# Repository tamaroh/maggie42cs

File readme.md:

# Maggie42cs

Maggie42csは42キー分割型の自作キーボードです。
- 左右対称カラムスタッガード
- Alice配列に似た、自然にハの字に手が配置されるデザイン
- MX Cherry 互換スイッチ、Kailh Choc v1, v2スイッチの3種に対応
- Extension キーはキーキャップセットで揃いやすい1.25U, 1.5Uに対応

## 必要なもの

| 部品名称                | 数量（両手分）                 | 備考                                   | 主な購入先                                                          |
| ----------------------  | ------------------------------ | -------------------------------------- | ------------------------------------------------------------------- |
| PCB                     | 1                              | サポートを折って左右に分けます         |                                                                     |
| トッププレート          | 2                              | 猫のシルエットがあるのが左側           |                                                                     |
| ボトムプレート          | 2                              | 左右の差はありません                   |                                                                     |
| ネジ                    | 24                             | M2                                     |                                                                     |
| 丸スペーサー            | 12                             | 5mm or 7.5mm                           |                                                                     |
| ゴム足                  | 8                              |                                        |                                                                     |
| スイッチソケット        | 42                             | Cherry MX / Kailh choc 対応のもの      | [TALP KEYBOARD](https://shop.talpkeyboard.com) など                 |
| メカニカルスイッチ      | 42                             | Cherry MX / Kailh choc V1 / V2 対応*   | [遊舎工房](https://shop.yushakobo.jp/collections/all-switches) など |
| キーキャップ            | 1U x 33, 1.25U x 7, 1.5U x 2   | スイッチに対応したもの                 | [遊舎工房](https://shop.yushakobo.jp/collections/keycaps) など      |
| TRSコネクター           | 2                              | PJ-399B-6A                             | [LCSC](https://www.lcsc.com/) など                                  |
| 3.5mmオーディオケーブル | 1                              | TRRS（4極）またはTRS（3極）            | [TALP KEYBOARD](https://shop.talpkeyboard.com) など                 |
| USBケーブル             | 1                              | 機器側がTypeCのもの                    | 家電量販店など                                                      |

## 使用する工具など

- はんだ付け工具
  - こて、こて台、こて先クリーナー、はんだ線など
- 精密ドライバー

## あると便利なもの

- ピンセット
- キースイッチプラー
- キーキャッププラー
- はんだ吸い取り線または吸い取り器
- 絶縁耐熱テープ
- 
## 製作手順

1. PCBのサポート部分を折り取ります。折った部分のデコボコが気になる場合はやすりなどで削ってください。
   
1. ソケットをはんだ付けします。  
   MXスイッチ用のソケットは上側、Chocスイッチ用のソケットは下側に設置します。  
   印刷に合わせて、スイッチの穴を塞がないようにします。
   
1. TRSコネクターをはんだ付けします。  
   ずれやすいのでテープなどで固定してください。  
   
1. ファームウェアのファイル（.uf2）をダウンロードします。  
   https://github.com/tamaroh/maggie42cs/releases/tag/V2.0.2
1. （片側ずつ両方とも）USBケーブルを接続して、以下のいずれかの方法で `RPI-RP2` リムーバブルドライブをマウントさせます。
   1. BOOTSELボタンを押しながら、USBケーブルを接続します。
   1. USBケーブルを接続してから、BOOTSELボタンを押しながらRESETボタンを押します。
   1. 左側はTABキー、右側はYキーを押したままUSBケーブルを接続します（キースイッチ装着済みの場合）。
   
1. （片側ずつ両方とも）マウントされた `RPI-RP2` ドライブ内にファームウェアのファイルをコピーして保存します。
   自動的にマウントが解除され、キーボードが再起動します。
   再起動したら、一度USBケーブルを抜いてください。
1. キースイッチを数個、先にキープレートに差し込みます。キープレートの表裏は印字以外にはありません。
   
1. スイッチのピンがソケットに合うように上からまっすぐ抑え、基板と接続して位置を合わせます。

1. 残りのスイッチを差し込みます。ソケットとスイッチを指で挟み込むようにして、ソケットに確実に差し込みます。
1. 基板を裏返し、ソケットからスイッチの端子の先端が見えることを確認してください。見えない場合はスイッチのピンが曲がっているか、ソケットの不良です。
   
1. ネジとスペーサーをトッププレートにネジ止めします。(片側6箇所) 
1. ボトムプレートをネジ止めし、ゴム足を取り付けます。
1. キーキャップを取り付けます。
1. TRRSケーブルを接続して、できあがり

## キーマップを変更する

Maggie42は[Remap](https://remap-keys.app)によるキーマップ変更に対応しています。  
ハードウェア接続のあとJSONファイルを要求される場合は[ファームウェアと同じ場所](https://github.com/tamaroh/maggie42cs/releases/tag/V2.0.2)からダウンロードして使用してください。

## 注意事項

- 必要な手順や部品の種類・数はアップデートによって変更になる場合があります。
- 本ビルドガイドの写真の一部は製品と異なる場合があります。

## 実装の差異について

キーケット2026にて販売した一部のキットは、製作の時期により差異があります。
- 4極の3.5mmコネクターを使用しています（はんだ実装済みです）。TRS（3極）ケーブルではなくTRRS（4極）ケーブルが必要です。
- 左右でPCBの印字の色が異なります。
  
- 手順通りのファームウェアとは異なります。書き込み済みで販売いたしましたが、再度セットアップする場合は[V2.0.0のファームウェア](https://github.com/tamaroh/maggie42cs/releases/tag/V2.0.0)を使用してください。
- Remapにアクセスした際は「maggie42csv2」と表示されます。

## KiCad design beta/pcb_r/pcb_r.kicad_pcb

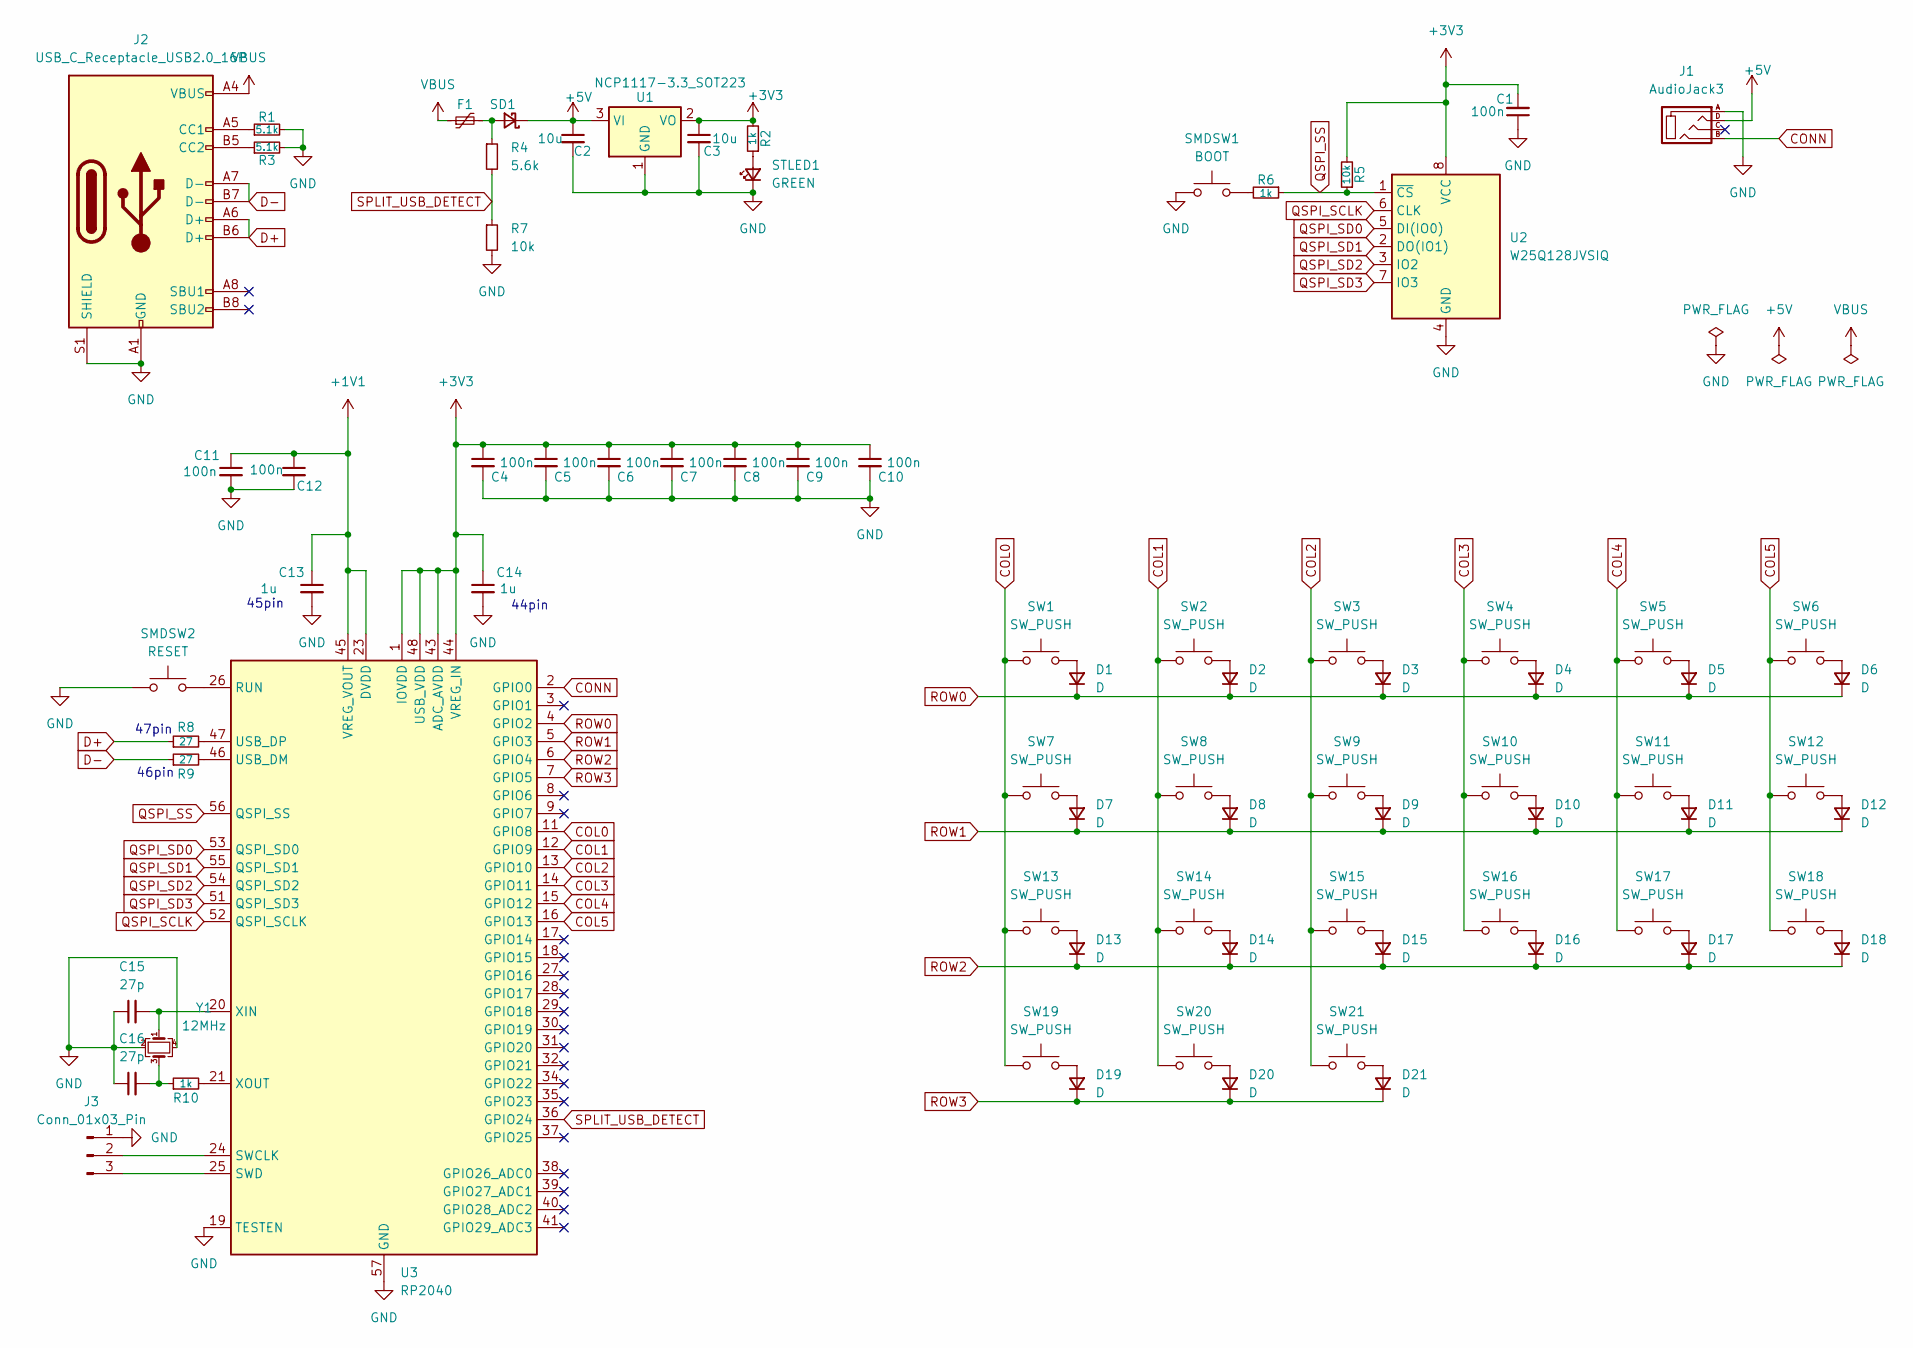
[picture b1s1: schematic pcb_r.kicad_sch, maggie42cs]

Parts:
C1, C4, C5, C6, C7, C8, C9, C10, C11, C12: 100n; C_0402_1005Metric; LCSC C1525
C2, C3: 10u; C_0402_1005Metric; LCSC C15525
C13, C14: 1u; C_0402_1005Metric; LCSC C52923
C15, C16: 27p; C_0402_1005Metric; LCSC C1557
D1, D2, D3, D4, D5, D6, D7, D8, D9, D10, D11, D12, D13, D14, D15, D16, D17, D18, D19, D20, D21: D; D_SOD-123; LCSC C81598
F1: Fuse_0603_1608Metric; LCSC C2757930
J1: AudioJack3; MJ-4PP-9_1side; LCSC C22459514
J2: USB_C_Receptacle_USB2.0_16P; USB_C_Receptacle_HRO_TYPE-C-31-M-12; LCSC C165948
J3: Conn_01x03_Pin; PinHeader_1x03_P1.27mm_Vertical
R1, R3: 5.1k; R_0402_1005Metric; LCSC C25905
R2, R6, R10: 1k; R_0402_1005Metric; LCSC C11702
R4: 5.6k; R_0402_1005Metric; LCSC C25908
R5, R7: 10k; R_0402_1005Metric; LCSC C25744
R8, R9: 27; R_0402_1005Metric; LCSC C25100
SD1: D_SOD-123; LCSC C8598
SMDSW1: BOOT; TS-1088R-02026; LCSC C455280
SMDSW2: RESET; TS-1088R-02026; LCSC C455280
STLED1: GREEN; LED_0402_1005Metric; LCSC C130723
SW1, SW2, SW3, SW4, SW5, SW7, SW8, SW9, SW10, SW11, SW12, SW13, SW14, SW15, SW16, SW17, SW20: SW_PUSH; keyswitch_cherrymx_choc12_hotswap_1u
SW6: SW_PUSH; keyswitch_cherrymx_choc12_hotswap_1.5u
SW18, SW19, SW21: SW_PUSH; keyswitch_cherrymx_choc12_hotswap_1.25u
U1: NCP1117-3.3_SOT223; SOT-223-3_TabPin2; LCSC C347222
U2: W25Q128JVSIQ; SOIC-8W_5.3x5.3mm_P1.27mm; LCSC C97521
U3: RP2040; QFN-56-1EP_7x7mm_P0.4mm_EP3.2x3.2mm; LCSC C2040
Y1: 12MHz; Crystal_SMD_SeikoEpson_TSX3225-4Pin_3.2x2.5mm; LCSC C91749

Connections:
+1V1: C11.1, C12.1, C13.1, U3.23 (DVDD), U3.45 (VREG_VOUT), U3.50 (DVDD)
+3V3: C1.2, C3.1, C4.1, C5.1, C6.1, C7.1, C8.1, C9.1, C10.1, C14.1, R2.2, R5.2, U1.2 (VO), U2.8 (VCC), U3.1 (IOVDD), U3.10 (IOVDD), U3.22 (IOVDD), U3.33 (IOVDD), U3.42 (IOVDD), U3.43 (ADC_AVDD), U3.44 (VREG_IN), U3.48 (USB_VDD), U3.49 (IOVDD)
+5V: C2.1, J1.D, SD1.1 (K), U1.3 (VI)
COL0: SW1.1, SW7.1, SW13.1, SW19.1, U3.11 (GPIO8)
COL1: SW2.1, SW8.1, SW14.1, SW20.1, U3.12 (GPIO9)
COL2: SW3.1, SW9.1, SW15.1, SW21.1, U3.13 (GPIO10)
COL3: SW4.1, SW10.1, SW16.1, U3.14 (GPIO11)
COL4: SW5.1, SW11.1, SW17.1, U3.15 (GPIO12)
COL5: SW6.1, SW12.1, SW18.1, U3.16 (GPIO13)
CONN: J1.B, U3.2 (GPIO0)
D+: J2.A6 (D+), J2.B6 (D+), R8.1
D-: J2.A7 (D-), J2.B7 (D-), R9.1
GND: C1.1, C2.2, C3.2, C4.2, C5.2, C6.2, C7.2, C8.2, C9.2, C10.2, C11.2, C12.2, C13.2, C14.2, C15.1, C16.1, J1.A, J2.A1 (GND), J2.A12 (GND), J2.B1 (GND), J2.B12 (GND), J2.S1 (SHIELD), J3.1, R1.2, R3.2, R7.2, SMDSW1.1, SMDSW2.1, STLED1.1 (K), U1.1 (GND), U2.4 (GND), U3.19 (TESTEN), U3.57 (GND), Y1.2, Y1.4
unnamed: C16.2, R10.1, Y1.3
unnamed: D1.2 (A), SW1.2
unnamed: D2.2 (A), SW2.2
unnamed: D3.2 (A), SW3.2
unnamed: D4.2 (A), SW4.2
unnamed: D5.2 (A), SW5.2
unnamed: D6.2 (A), SW6.2
unnamed: D7.2 (A), SW7.2
unnamed: D8.2 (A), SW8.2
unnamed: D9.2 (A), SW9.2
unnamed: D10.2 (A), SW10.2
unnamed: D11.2 (A), SW11.2
unnamed: D12.2 (A), SW12.2
unnamed: D13.2 (A), SW13.2
unnamed: D14.2 (A), SW14.2
unnamed: D15.2 (A), SW15.2
unnamed: D16.2 (A), SW16.2
unnamed: D17.2 (A), SW17.2
unnamed: D18.2 (A), SW18.2
unnamed: D19.2 (A), SW19.2
unnamed: D20.2 (A), SW20.2
unnamed: D21.2 (A), SW21.2
unnamed: J2.A5 (CC1), R1.1
unnamed: J2.B5 (CC2), R3.1
unnamed: J3.2, U3.24 (SWCLK)
unnamed: J3.3, U3.25 (SWD)
unnamed: R6.2, SMDSW1.2
unnamed: F1.2, R4.1, SD1.2 (A)
unnamed: R2.1, STLED1.2 (A)
unnamed: SMDSW2.2, U3.26 (RUN)
unnamed: R9.2, U3.46 (USB_DM)
unnamed: R8.2, U3.47 (USB_DP)
unnamed: C15.2, U3.20 (XIN), Y1.1
unnamed: R10.2, U3.21 (XOUT)
QSPI_SCLK: U2.6 (CLK), U3.52 (QSPI_SCLK)
QSPI_SD0: U2.5 (DI(IO0)), U3.53 (QSPI_SD0)
QSPI_SD1: U2.2 (DO(IO1)), U3.55 (QSPI_SD1)
QSPI_SD2: U2.3 (IO2), U3.54 (QSPI_SD2)
QSPI_SD3: U2.7 (IO3), U3.51 (QSPI_SD3)
QSPI_SS: R5.1, R6.1, U2.1 (~CS), U3.56 (QSPI_SS)
ROW0: D1.1 (K), D2.1 (K), D3.1 (K), D4.1 (K), D5.1 (K), D6.1 (K), U3.4 (GPIO2)
ROW1: D7.1 (K), D8.1 (K), D9.1 (K), D10.1 (K), D11.1 (K), D12.1 (K), U3.5 (GPIO3)
ROW2: D13.1 (K), D14.1 (K), D15.1 (K), D16.1 (K), D17.1 (K), D18.1 (K), U3.6 (GPIO4)
ROW3: D19.1 (K), D20.1 (K), D21.1 (K), U3.7 (GPIO5)
SPLIT_USB_DETECT: R4.2, R7.1, U3.36 (GPIO24)
VBUS: F1.1, J2.A4 (VBUS), J2.A9 (VBUS), J2.B4 (VBUS), J2.B9 (VBUS)

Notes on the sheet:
47pin
45pin
44pin
46pin

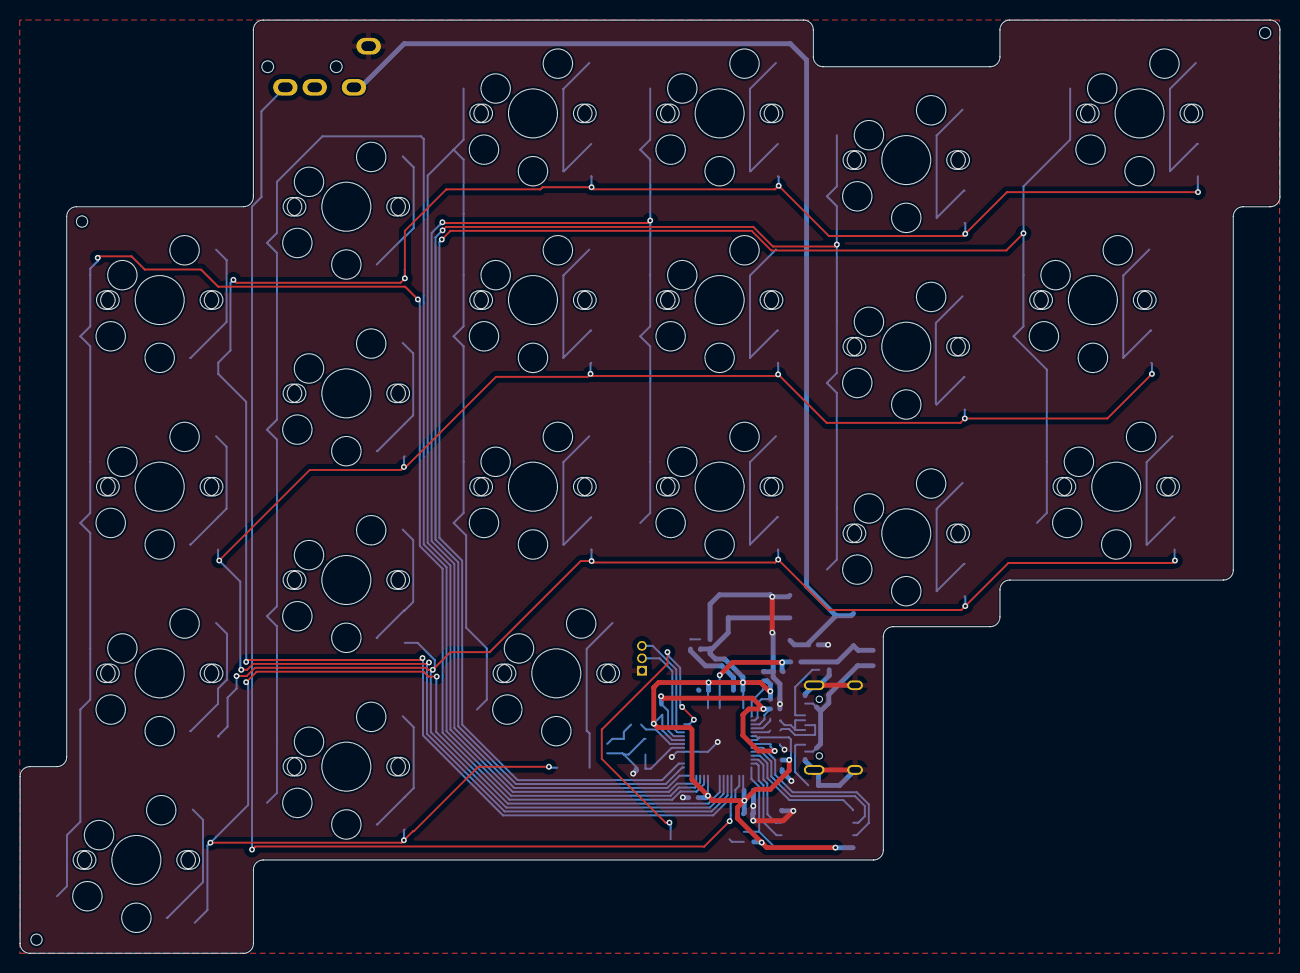
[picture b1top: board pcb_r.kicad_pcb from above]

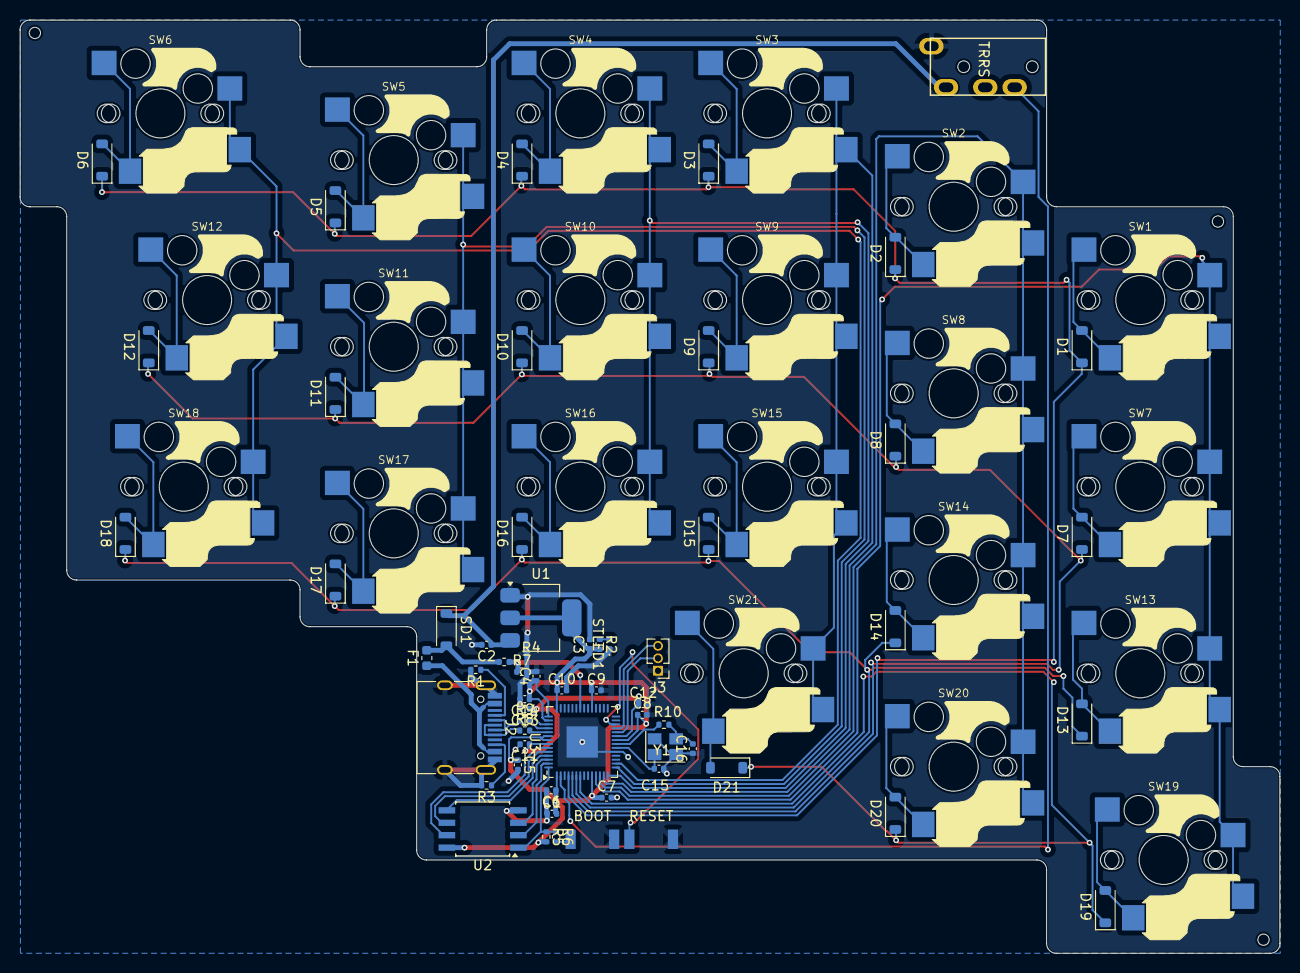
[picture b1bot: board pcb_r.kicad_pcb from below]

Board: 2 copper layers, 128.6 x 95.2 mm, 80 parts (80 on the bottom side), 59 nets.

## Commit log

2023-12-27 added gitignore for kicad
2023-12-27 created pcbs
2023-12-27 added readme
2024-01-24 complete
2024-10-23 added v2.0.0, failed
2024-10-25 create v2 init, v2.json for VIA
2024-11-10 fixed pid
2024-11-12 update readme (wip)
2024-11-12 add firmware files with readme updated
2024-11-12 add firmware url to readme
2024-11-19 1.1: create garbar files, 2.0: create left pcb
2024-11-23 update: 2.0.1_pcb_l
2024-12-28 WIP: v2 refactoring
2024-12-28 refactor: change folder name, old data is no maggie42cs0
2025-01-11 wip: layout
2025-02-17 add: pcb and plate garber files
2025-02-18 add readme
2025-03-08 add: images
2025-03-08 fix: image url
2026-03-24 add production files
2026-03-24 added v200 description
2026-03-30 add description about old connector
